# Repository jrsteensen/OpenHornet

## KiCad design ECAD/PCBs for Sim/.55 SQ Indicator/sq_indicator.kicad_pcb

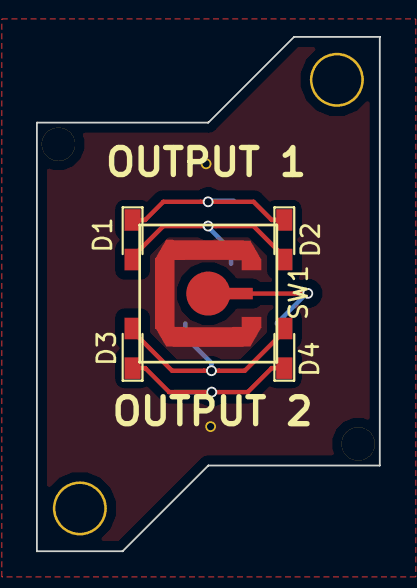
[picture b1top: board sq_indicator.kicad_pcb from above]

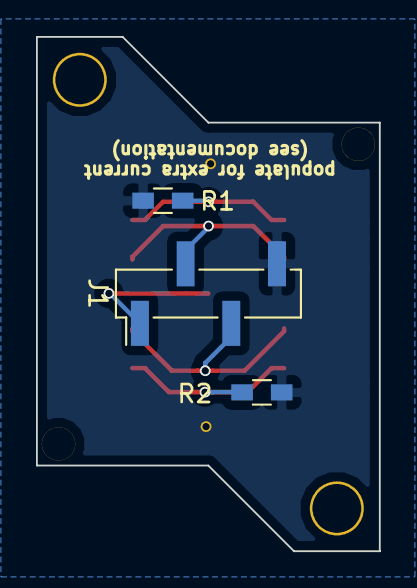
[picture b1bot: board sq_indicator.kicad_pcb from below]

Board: 2 copper layers, 19.1 x 28.6 mm, 8 parts (3 on the bottom side), 6 nets.

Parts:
D1, D2, D3, D4: LED; LED_0603_HandSoldering
J1: Conn_01x04; Pin_Header_Straight_1x04_Pitch2.54mm_SMD_Pin1Left
R1, R2: 68; R_0603_HandSoldering
SW1: push; SWITCH_SNAP_DOME_6.3mm_DIA_SINGLE_SIDE_PCB

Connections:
/backlight_1: D1.2, D2.2, J1.2
/backlight_2: D3.2, D4.2, J1.3
/button: J1.1, SW1.1
GND: J1.4, R1.1, R2.1, SW1.2
unnamed: D1.1, D2.1, R1.2
unnamed: D3.1, D4.1, R2.2

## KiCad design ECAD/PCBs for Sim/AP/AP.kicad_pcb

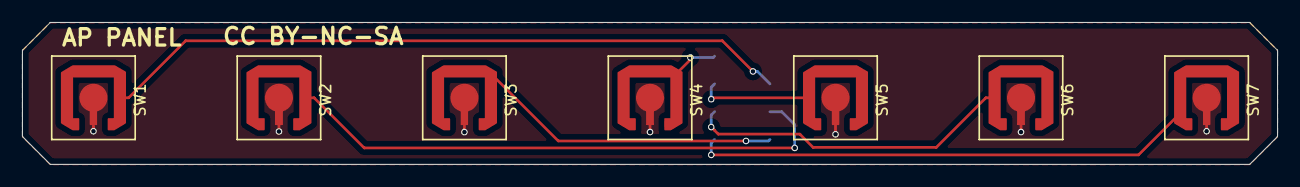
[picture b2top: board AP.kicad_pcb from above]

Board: 2 copper layers, 114.6 x 13.0 mm, 8 parts (1 on the bottom side), 8 nets.

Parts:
J1: Conn_02x04_Odd_Even; Pin_Header_Straight_2x04_Pitch2.54mm_SMD
SW1, SW2, SW3, SW4, SW5, SW6, SW7: SW_SPST; SWITCH_SNAP_DOME_6.3mm_DIA_SINGLE_SIDE_PCB

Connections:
unnamed: J1.1, SW1.1, SW2.1, SW3.1, SW4.1, SW5.1, SW6.1, SW7.1
unnamed: J1.2, SW4.2
unnamed: J1.3, SW1.2
unnamed: J1.4, SW5.2
unnamed: J1.5, SW2.2
unnamed: J1.6, SW6.2
unnamed: J1.7, SW3.2
unnamed: J1.8, SW7.2

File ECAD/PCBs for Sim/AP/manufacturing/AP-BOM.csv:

"Id";"Designator";"Package";"Quantity";"Designation";"Supplier and ref";
1;"SW1,SW2,SW3,SW4,SW5,SW6,SW7";"SWITCH_SNAP_DOME_6.3mm_DIA_SINGLE_SIDE_PCB";7;"SW_SPST";;;
2;"G***";"CC-BY-NC-SA-Small";1;"LOGO";;;
3;"G***";"OH_LOGO_37.7mm_5.9mm";1;"LOGO";;;
4;"J1";"Pin_Header_Straight_2x04_Pitch2.54mm_SMD";1;"Conn_02x04_Odd_Even";;;

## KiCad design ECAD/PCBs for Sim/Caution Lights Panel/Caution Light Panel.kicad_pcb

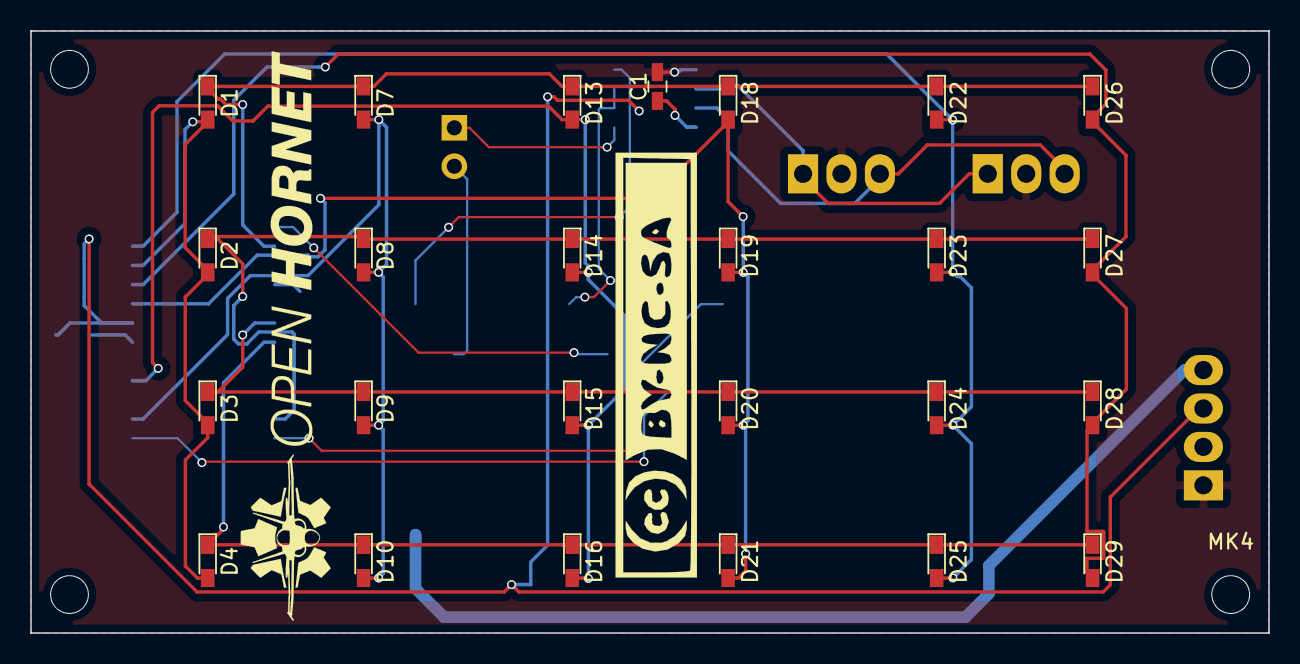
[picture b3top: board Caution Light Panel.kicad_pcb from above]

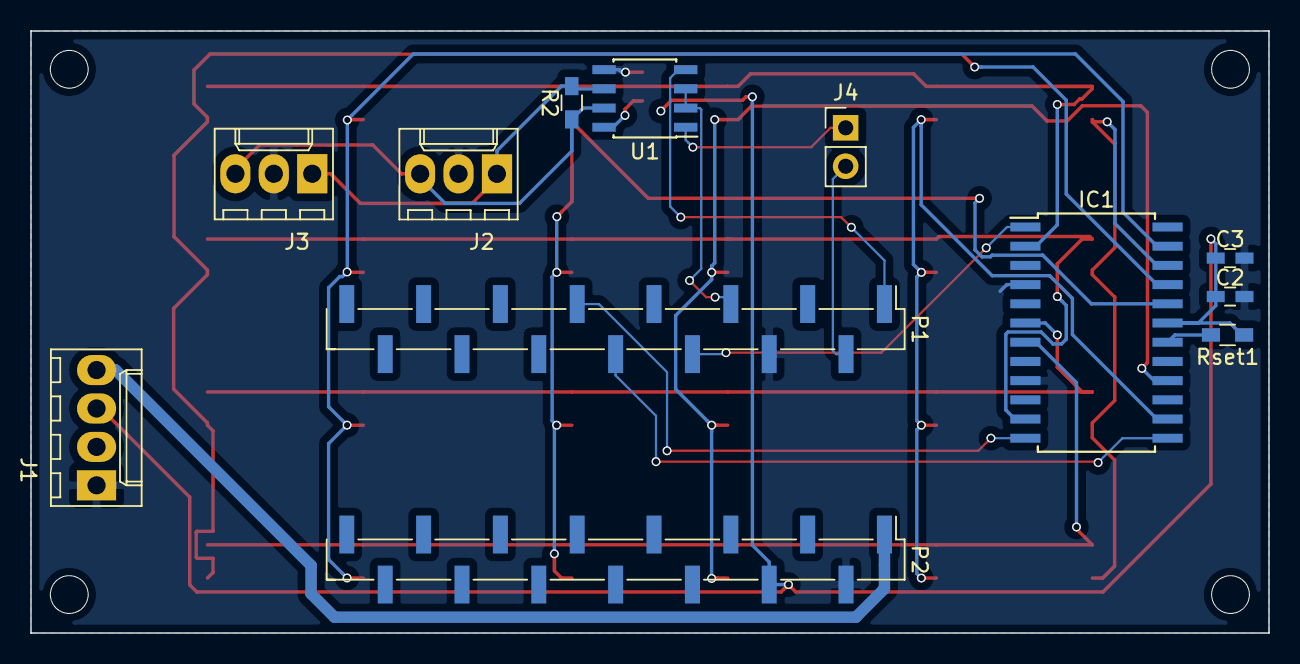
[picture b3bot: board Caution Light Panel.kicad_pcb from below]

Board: 2 copper layers, 81.9 x 39.8 mm, 41 parts (12 on the bottom side), 23 nets.

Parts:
C1: 0.1uF; C_0603_HandSoldering
C2: 100nF; C_0603_HandSoldering
C3: 47uF; C_0603_HandSoldering
D1: 0,0; LED_0603_HandSoldering
D2: 1,0; LED_0603_HandSoldering
D3: 2,0; LED_0603_HandSoldering
D4: 3,0; LED_0603_HandSoldering
D7: 0,1; LED_0603_HandSoldering
D8: 1,1; LED_0603_HandSoldering
D9: 2,1; LED_0603_HandSoldering
D10: 3,1; LED_0603_HandSoldering
D13: 0,2; LED_0603_HandSoldering
D14: 1,2; LED_0603_HandSoldering
D15: 2,2; LED_0603_HandSoldering
D16: 3,2; LED_0603_HandSoldering
D18: 0,3; LED_0603_HandSoldering
D19: 1.3; LED_0603_HandSoldering
D20: 2,3; LED_0603_HandSoldering
D21: 3,3; LED_0603_HandSoldering
D22: 0.4; LED_0603_HandSoldering
D23: 1.4; LED_0603_HandSoldering
D24: 2,4; LED_0603_HandSoldering
D25: 3,4; LED_0603_HandSoldering
D26: 0.5; LED_0603_HandSoldering
D27: 1.5; LED_0603_HandSoldering
D28: 2,5; LED_0603_HandSoldering
D29: 3,5; LED_0603_HandSoldering
IC1: MAX7219; SOIC-24W_7.5x15.4mm_Pitch1.27mm
J1: PWR; Molex_KK-6410-04_04x2.54mm_Straight
J2: BUS IN; Molex_KK-6410-03_03x2.54mm_Straight
J3: BUS OUT; Molex_KK-6410-03_03x2.54mm_Straight
J4: PGM ENBLE; Pin_Header_Straight_1x02_Pitch2.54mm
MK1, MK2, MK3, MK4: Mounting_Hole; MountingHole_2.5mm
P1: Digital; Pin_Header_Straight_1x15_Pitch2.54mm_SMD_Pin1Left
P2: Analog; Pin_Header_Straight_1x15_Pitch2.54mm_SMD_Pin1Left
R2: 120; R_0603_HandSoldering
Rset1: 30K; R_0603_HandSoldering
U1: MAX487EESA; SOIC-8_3.9x4.9mm_Pitch1.27mm

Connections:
+5V: C1.1, C2.1, C3.1, IC1.19, J1.3, P2.4, Rset1.1, U1.8
+12V: J1.4, P2.1
/0(Rx): J4.2, P1.2
/1(Tx): P1.1, U1.4
/2: P1.5, U1.2, U1.3
/3(**): IC1.1, P1.6
/5(**): IC1.13, P1.8
/6(**): IC1.12, P1.9
/Dig0: D1.1, D7.1, D13.1, D18.1, D22.1, D26.1, IC1.2
/Dig1: D2.1, D8.1, D14.1, D19.1, D23.1, D27.1, IC1.11
/Dig2: D3.1, D9.1, D15.1, D20.1, D24.1, D28.1, IC1.6
/Dig3: D4.1, D10.1, D16.1, D21.1, D25.1, D29.1, IC1.7
/RX_ENABLE: J4.1, U1.1
/SegA: D7.2, D8.2, D9.2, D10.2, IC1.14
/SegB: D13.2, D14.2, D15.2, D16.2, IC1.16
/SegC: D18.2, D19.2, D20.2, D21.2, IC1.20
/SegD: D22.2, D23.2, D24.2, D25.2, IC1.23
/SegDP: D1.2, D2.2, D3.2, D4.2, IC1.22
/SegE: D26.2, D27.2, D28.2, D29.2, IC1.21
GND: C1.2, C2.2, C3.2, IC1.4, IC1.9, J1.1, J2.2, J3.2, P1.4, P2.2, U1.5
unnamed: IC1.18, Rset1.2
unnamed: J2.1, J3.1, R2.2, U1.6
unnamed: J2.3, J3.3, R2.1, U1.7

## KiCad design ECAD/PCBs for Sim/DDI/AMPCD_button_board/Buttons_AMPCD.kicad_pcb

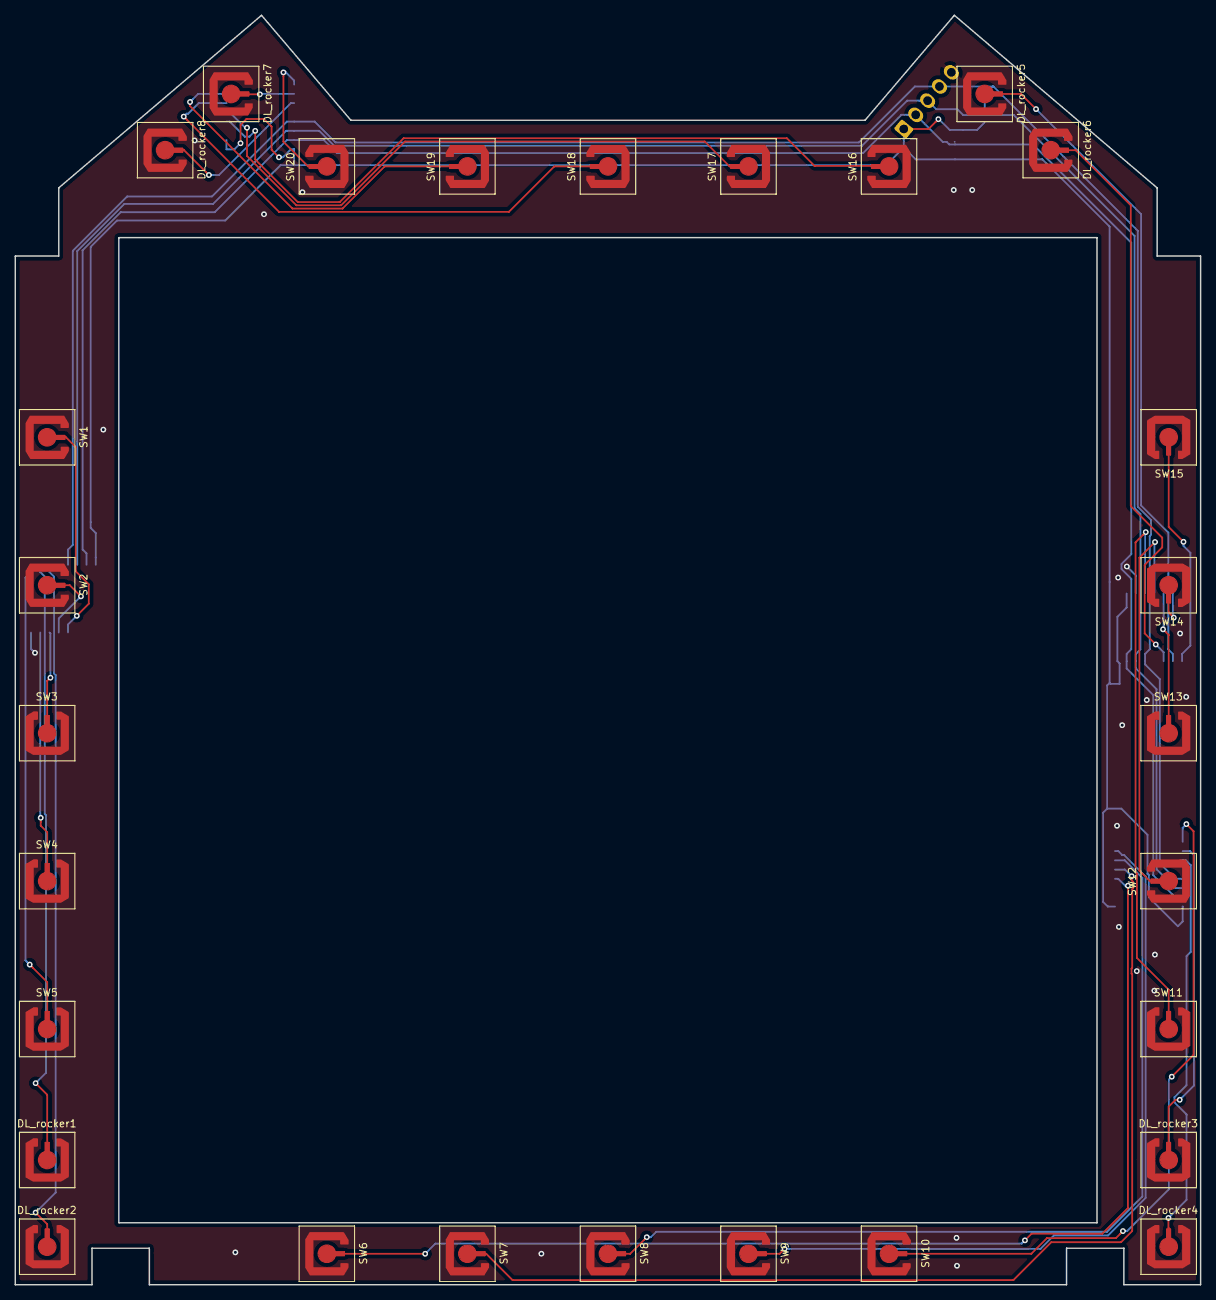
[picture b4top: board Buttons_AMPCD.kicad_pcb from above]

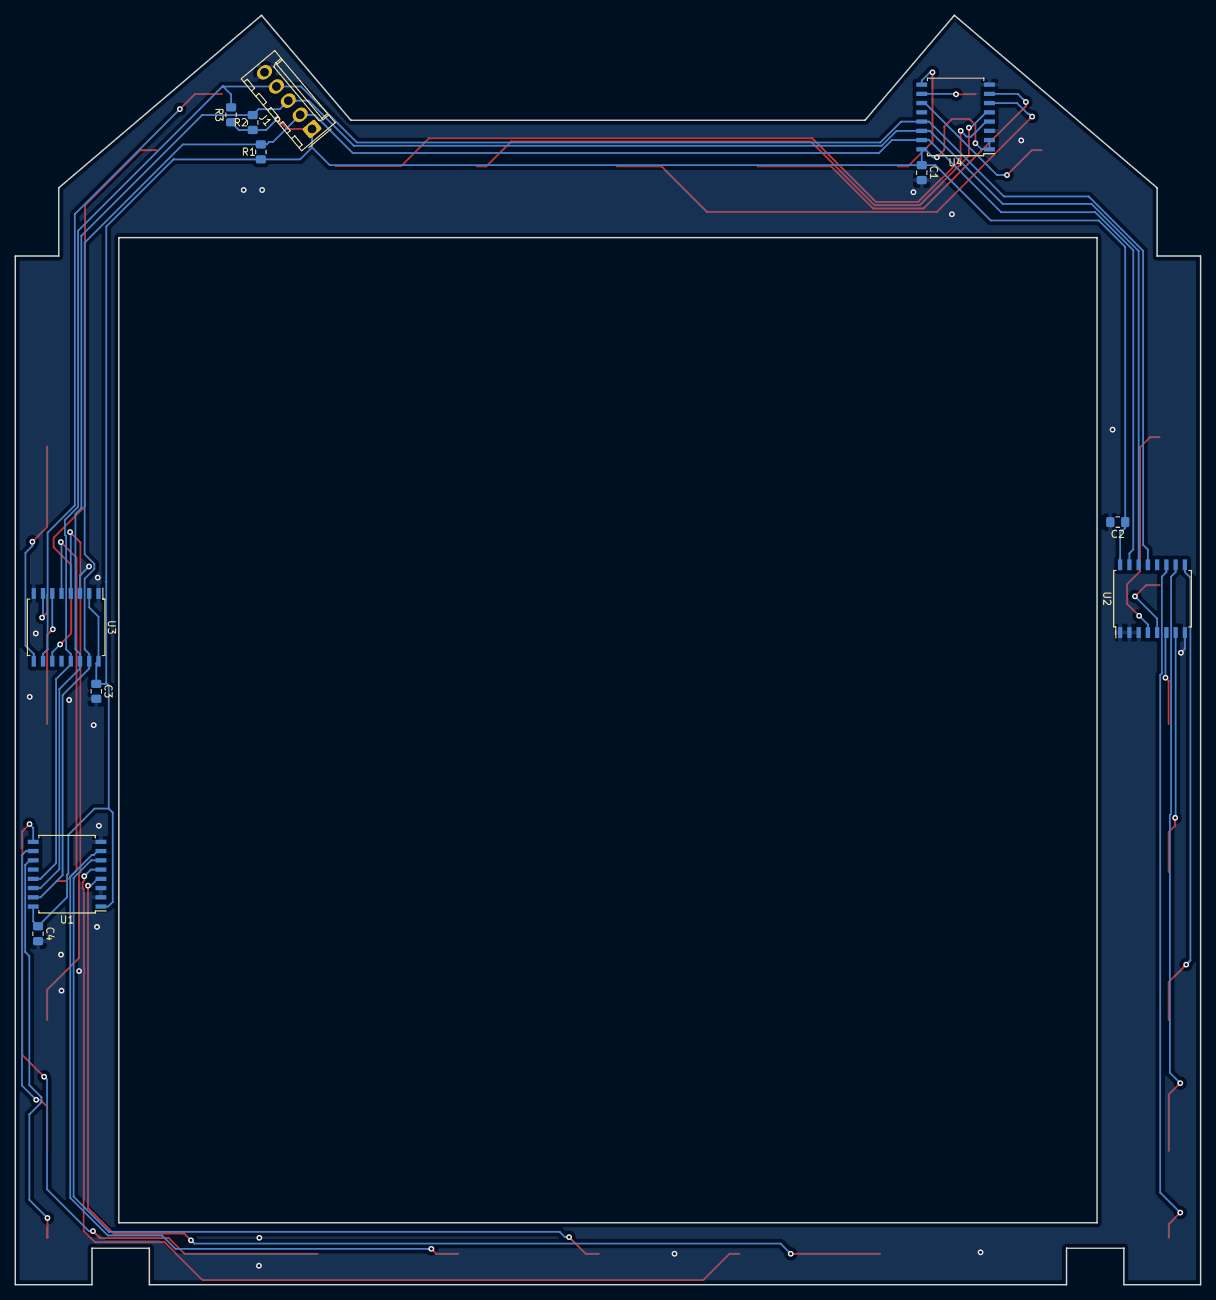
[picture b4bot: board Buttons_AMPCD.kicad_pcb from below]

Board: 2 copper layers, 162.8 x 174.4 mm, 40 parts (12 on the bottom side), 33 nets.

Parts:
C1, C2, C3, C4: 47uF; C_0805_2012Metric_Pad1.15x1.40mm_HandSolder
DL_rocker1, DL_rocker2, DL_rocker3, DL_rocker4, DL_rocker5, DL_rocker6, DL_rocker7, DL_rocker8: SW_Push; SWITCH_SNAP_DOME_6.3mm_DIA_SINGLE_SIDE_PCB
J1: ExpansionPort; Molex_KK-254_AE-6410-05A_1x05_P2.54mm_Vertical
R1, R2, R3: 1k; R_0805_2012Metric_Pad1.15x1.40mm_HandSolder
SW1, SW2, SW3, SW4, SW5, SW6, SW7, SW8, SW9, SW10, SW11, SW12, SW13, SW14, SW15, SW16, SW17, SW18, SW19, SW20: SW_Push; SWITCH_SNAP_DOME_6.3mm_DIA_SINGLE_SIDE_PCB
U1, U2, U3, U4: TCA9534; SOIC-16W_7.5x10.3mm_P1.27mm

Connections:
+5V: C1.1, C2.1, C3.1, C4.1, J1.1, R1.1, R2.1, R3.1, U1.1, U1.16, U2.16, U3.2, U3.16, U4.1, U4.2, U4.16
GND: C1.2, C2.2, C3.2, C4.2, DL_rocker1.2, DL_rocker2.2, DL_rocker3.2, DL_rocker4.2, DL_rocker5.2, DL_rocker6.2, DL_rocker7.2, DL_rocker8.2, J1.5, SW1.2, SW2.2, SW3.2, SW4.2, SW5.2, SW6.2, SW7.2, SW8.2, SW9.2, SW10.2, SW11.2, SW12.2, SW13.2, SW14.2, SW15.2, SW16.2, SW17.2, SW18.2, SW19.2, SW20.2, U1.2, U1.3, U1.8, U2.1, U2.2, U2.3, U2.8, U3.1, U3.3, U3.8, U4.3, U4.8
IRQ: J1.4, R3.2, U1.13, U2.13, U3.13, U4.13
unnamed: DL_rocker1.1, U2.10
unnamed: DL_rocker2.1, U2.11
unnamed: DL_rocker3.1, U1.10
unnamed: DL_rocker4.1, U1.11
unnamed: DL_rocker5.1, U3.10
unnamed: DL_rocker6.1, U3.11
unnamed: DL_rocker7.1, U4.10
unnamed: DL_rocker8.1, U4.11
unnamed: SW1.1, U2.4
unnamed: SW2.1, U2.5
unnamed: SW3.1, U2.6
unnamed: SW4.1, U2.7
unnamed: SW5.1, U2.9
unnamed: SW6.1, U1.4
unnamed: SW7.1, U1.5
unnamed: SW8.1, U1.6
unnamed: SW9.1, U1.7
unnamed: SW10.1, U1.9
unnamed: SW11.1, U3.4
unnamed: SW12.1, U3.5
unnamed: SW13.1, U3.6
unnamed: SW14.1, U3.7
unnamed: SW15.1, U3.9
unnamed: SW16.1, U4.4
unnamed: SW17.1, U4.5
unnamed: SW18.1, U4.6
unnamed: SW19.1, U4.7
unnamed: SW20.1, U4.9
SCL: J1.3, R2.2, U1.14, U2.14, U3.14, U4.14
SDA: J1.2, R1.2, U1.15, U2.15, U3.15, U4.15

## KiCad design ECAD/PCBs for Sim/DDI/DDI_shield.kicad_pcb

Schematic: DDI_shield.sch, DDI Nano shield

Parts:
C1: 0.1uF; C_0805_2012Metric_Pad1.15x1.40mm_HandSolder
J1: PWR; Molex_KK-254_AE-6410-04A_1x04_P2.54mm_Vertical
J2: BUS IN; Molex_KK-254_AE-6410-03A_1x03_P2.54mm_Vertical
J3: BUS OUT; Molex_KK-254_AE-6410-03A_1x03_P2.54mm_Vertical
J4: PGM SEL; Pin_Header_Straight_1x02_Pitch2.54mm
J5: POT1; Molex_KK-254_AE-6410-03A_1x03_P2.54mm_Vertical
J6: ExpansionPort; PinHeader_1x05_P2.54mm_Vertical
J7: POT2; Molex_KK-254_AE-6410-03A_1x03_P2.54mm_Vertical
J8: ROT SW; PinHeader_1x04_P2.54mm_Vertical
J9: CRS; PinHeader_1x03_P2.54mm_Vertical
J10: HDG; PinHeader_1x03_P2.54mm_Vertical
P1: Digital; Socket_Strip_Arduino_1x15
P2: Analog; Socket_Strip_Arduino_1x15
P3, P4, P5, P6: mounting; 1pin_Nano
R1: 120; R_0805_2012Metric_Pad1.15x1.40mm_HandSolder
R2, R3, R4, R5: 10k; R_0805_2012Metric_Pad1.15x1.40mm_HandSolder
U1: MAX487EESA; SOIC-8_3.9x4.9mm_Pitch1.27mm

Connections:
+3V3: J1.2, P2.14
+5V: C1.1, J1.3, J5.1, J6.1 (Power), J7.1, P2.4, R2.1, R4.1, U1.8
+12V: J1.4, P2.1
/0(Rx): J4.2, P1.2
/1(Tx): P1.1, U1.4
/2: P1.5, U1.2, U1.3
/3(**): J6.4 (IRQ), P1.6
/4: J6.2 (SDA), P1.7
/5(**): J6.3 (SCL), P1.8
/8: P1.11, R2.2, R3.1
/9(**): P1.12, R4.2, R5.1
/10(**/SS): J8.1, P1.13
/11(**/MOSI): J8.2, P1.14
/12(MISO): J8.3, P1.15
/A0: J5.2, P2.12
/A1: J7.2, P2.11
/A3: J9.1, P2.9
/A4: J9.3, P2.8
/A5: J10.1, P2.7
/A6: J10.3, P2.6
/AREF: P2.13
/RX_ENABLE: J4.1, U1.1
GND: C1.2, J1.1, J2.2, J3.2, J5.3, J6.5 (GND), J7.3, J8.4, J9.2, J10.2, P1.4, P2.2, R3.2, R5.2, U1.5
unnamed: J2.1, J3.1, R1.2, U1.6
unnamed: J2.3, J3.3, R1.1, U1.7

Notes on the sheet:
Holes
NANO CONNECTIONS
RS-485 BUS
1) INSTALL 120 OHM RESISTOR ACROSS A AND B OF MAX487 ONLY FOR BUS TERMINATION. 2) INSTALL JUMPER BETWEEN PIN 1 AND 2 OF PGM SEL FOR RS487 BUS ENABLE. REMOVE JUMPER FOR PROGRAMMING ARDUINO NANO. 3) SEE DOCUMENTATION FOR CONNECTIVITY AND CONFIGURATION.
NOTES: (UNLESS OTHERWISE SPECIFIED)
PWR IN
PWR FLAGS
Inputs
I2C addresses 0b0111000 0b0111001 0b0111010 0b0111011
DEVICE differentiation see documentation
13(SCK)
6(**)

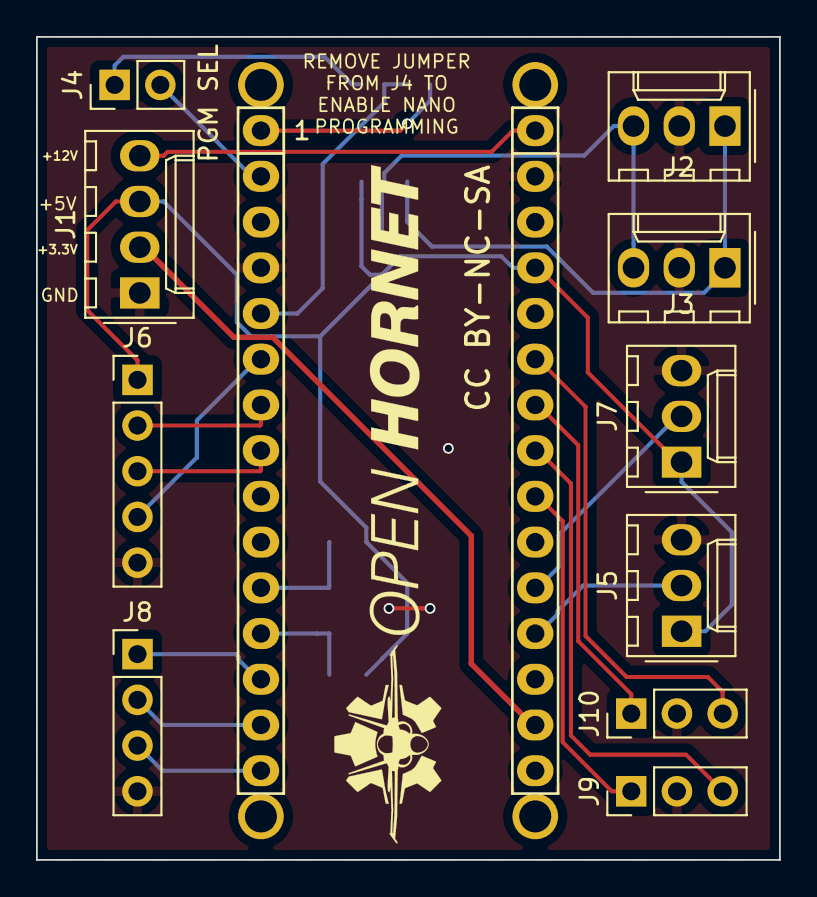
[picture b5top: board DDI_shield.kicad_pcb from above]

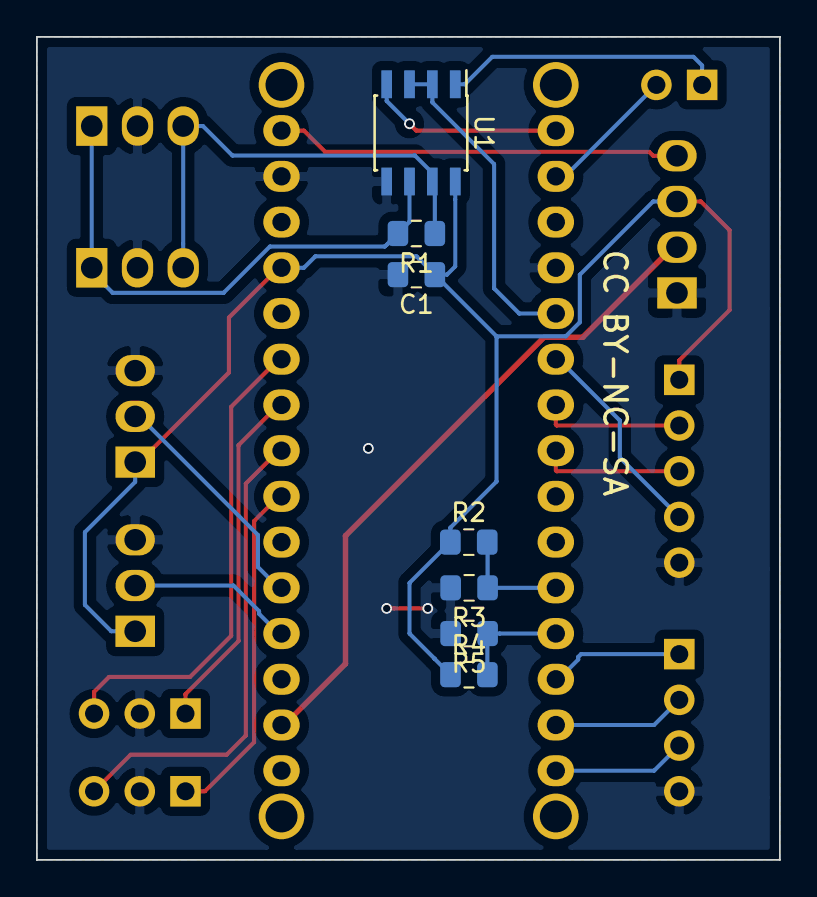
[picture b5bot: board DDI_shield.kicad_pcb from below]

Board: 2 copper layers, 41.3 x 45.7 mm, 23 parts (7 on the bottom side), 24 nets.

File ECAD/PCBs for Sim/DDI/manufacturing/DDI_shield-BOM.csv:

"Id";"Designator";"Package";"Quantity";"Designation";"Supplier and ref";
1;"G***";"OH_LOGO_37.7mm_5.9mm";1;"LOGO";;;
2;"J8";"PinHeader_1x04_P2.54mm_Vertical";1;"ROT SW";;;
3;"J4";"Pin_Header_Straight_1x02_Pitch2.54mm";1;"PGM SEL";;;
4;"P1";"Socket_Strip_Arduino_1x15";1;"Digital";;;
5;"P2";"Socket_Strip_Arduino_1x15";1;"Analog";;;
6;"P3,P4,P5,P6";"1pin_Nano";4;"mounting";;;
7;"U1";"SOIC-8_3.9x4.9mm_Pitch1.27mm";1;"MAX487EESA";;;
8;"J6";"PinHeader_1x05_P2.54mm_Vertical";1;"ExpansionPort";;;
9;"R2,R3,R4,R5";"R_0805_2012Metric_Pad1.15x1.40mm_HandSolder";4;"10k";;;
10;"C1";"C_0805_2012Metric_Pad1.15x1.40mm_HandSolder";1;"0.1uF";;;
11;"J1";"Molex_KK-254_AE-6410-04A_1x04_P2.54mm_Vertical";1;"PWR";;;
12;"J2";"Molex_KK-254_AE-6410-03A_1x03_P2.54mm_Vertical";1;"BUS IN";;;
13;"J3";"Molex_KK-254_AE-6410-03A_1x03_P2.54mm_Vertical";1;"BUS OUT";;;
14;"J5";"Molex_KK-254_AE-6410-03A_1x03_P2.54mm_Vertical";1;"POT1";;;
15;"J7";"Molex_KK-254_AE-6410-03A_1x03_P2.54mm_Vertical";1;"POT2";;;
16;"R1";"R_0805_2012Metric_Pad1.15x1.40mm_HandSolder";1;"120";;;
17;"J9";"PinHeader_1x03_P2.54mm_Vertical";1;"CRS";;;
18;"J10";"PinHeader_1x03_P2.54mm_Vertical";1;"HDG";;;

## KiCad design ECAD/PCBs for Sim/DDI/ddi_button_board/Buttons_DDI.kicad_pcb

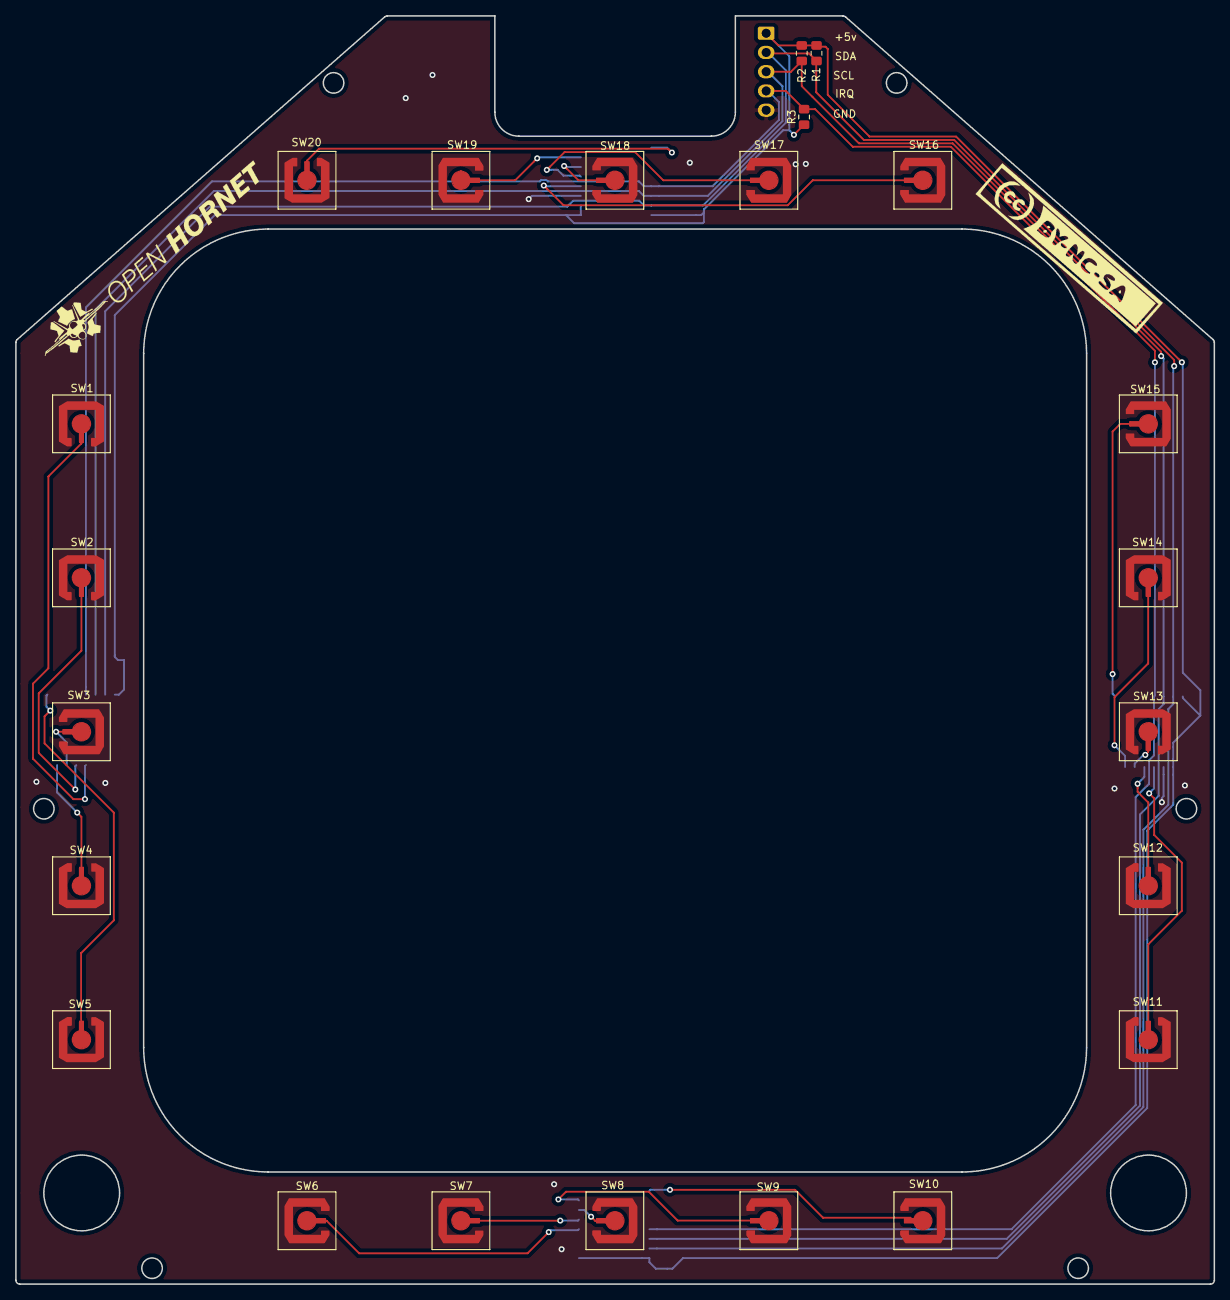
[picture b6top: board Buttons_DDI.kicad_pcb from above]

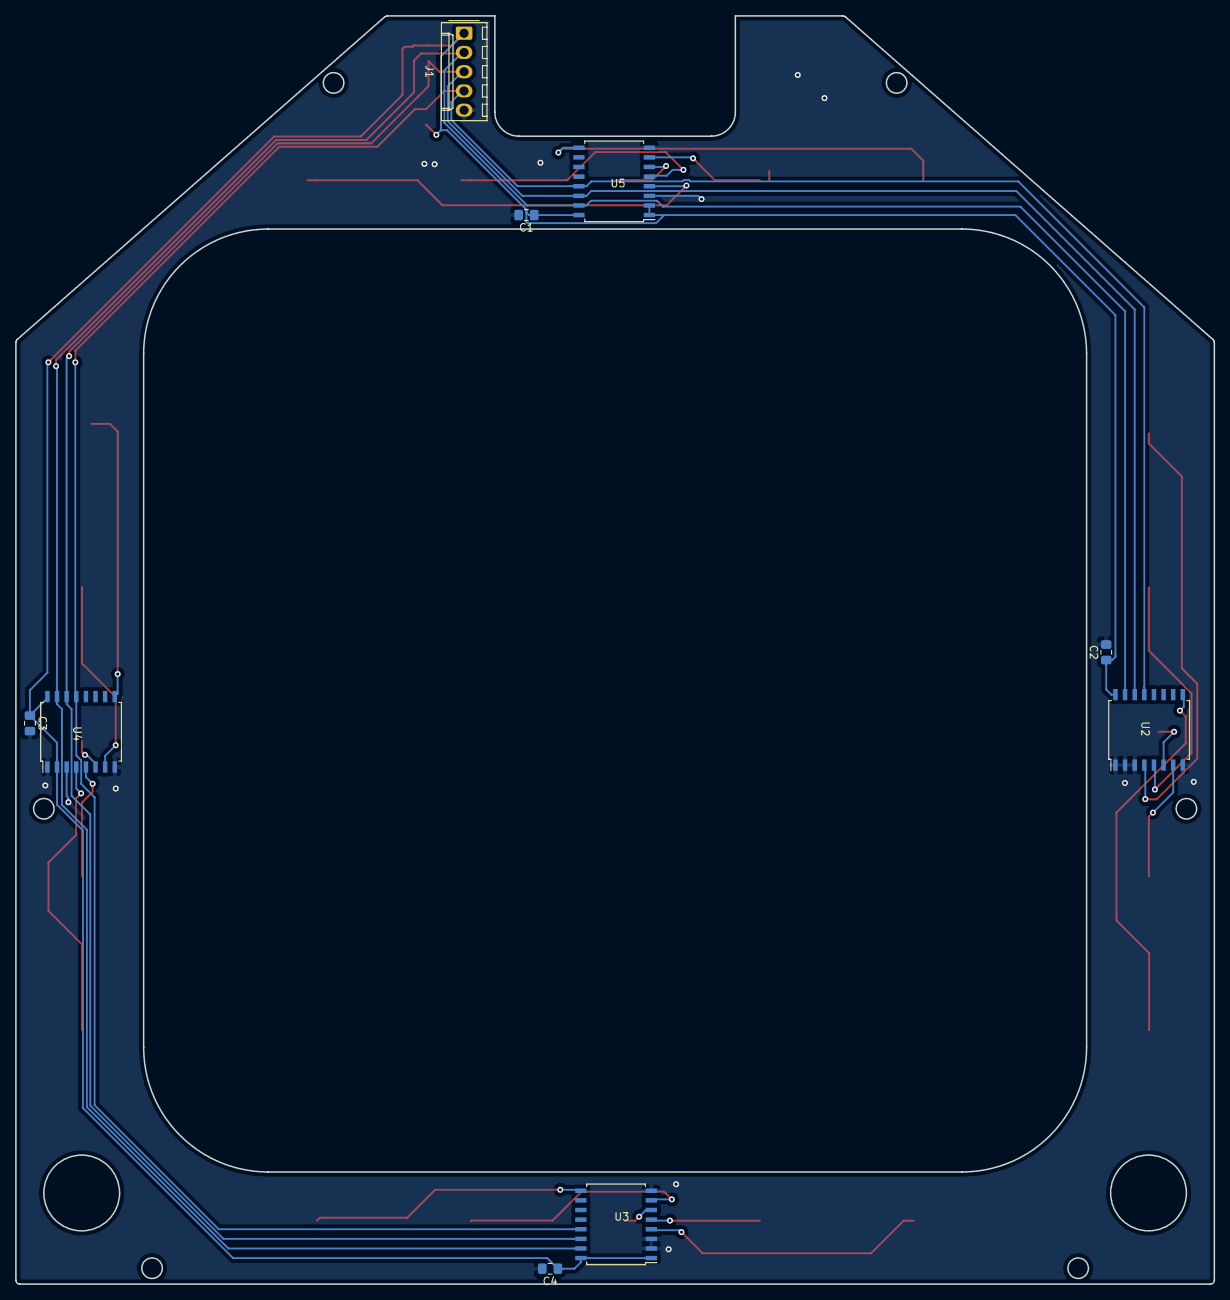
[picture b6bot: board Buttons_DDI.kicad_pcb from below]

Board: 2 copper layers, 158.2 x 167.4 mm, 32 parts (9 on the bottom side), 25 nets.

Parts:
C1, C2, C3, C4: 47uF; C_0805_2012Metric_Pad1.15x1.40mm_HandSolder
J1: ExpansionPort; Molex_KK-254_AE-6410-05A_1x05_P2.54mm_Vertical
R1, R2, R3: 1k; R_0805_2012Metric_Pad1.15x1.40mm_HandSolder
SW1, SW2, SW3, SW4, SW5, SW6, SW7, SW8, SW9, SW10, SW11, SW12, SW13, SW14, SW15, SW16, SW17, SW18, SW19, SW20: SW_Push; SWITCH_SNAP_DOME_6.3mm_DIA_SINGLE_SIDE_PCB
U2, U3, U4, U5: TCA9534; SOIC-16W_7.5x10.3mm_P1.27mm

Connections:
+5V: C1.1, C2.1, C3.1, C4.1, J1.1, R1.1, R2.1, R3.1, U2.16, U3.1, U3.16, U4.2, U4.16, U5.1, U5.2, U5.16
GND: C1.2, C2.2, C3.2, C4.2, J1.5, SW1.2, SW2.2, SW3.2, SW4.2, SW5.2, SW6.2, SW7.2, SW8.2, SW9.2, SW10.2, SW11.2, SW12.2, SW13.2, SW14.2, SW15.2, SW16.2, SW17.2, SW18.2, SW19.2, SW20.2, U2.1, U2.2, U2.3, U2.8, U3.2, U3.3, U3.8, U4.1, U4.3, U4.8, U5.3, U5.8
IRQ: J1.4, R3.2, U2.13, U3.13, U4.13, U5.13
unnamed: SW1.1, U2.4
unnamed: SW2.1, U2.5
unnamed: SW3.1, U2.6
unnamed: SW4.1, U2.7
unnamed: SW5.1, U2.9
unnamed: SW6.1, U3.4
unnamed: SW7.1, U3.5
unnamed: SW8.1, U3.6
unnamed: SW9.1, U3.7
unnamed: SW10.1, U3.9
unnamed: SW11.1, U4.4
unnamed: SW12.1, U4.5
unnamed: SW13.1, U4.6
unnamed: SW14.1, U4.7
unnamed: SW15.1, U4.9
unnamed: SW16.1, U5.4
unnamed: SW17.1, U5.5
unnamed: SW18.1, U5.6
unnamed: SW19.1, U5.7
unnamed: SW20.1, U5.9
SCL: J1.3, R2.2, U2.14, U3.14, U4.14, U5.14
SDA: J1.2, R1.2, U2.15, U3.15, U4.15, U5.15

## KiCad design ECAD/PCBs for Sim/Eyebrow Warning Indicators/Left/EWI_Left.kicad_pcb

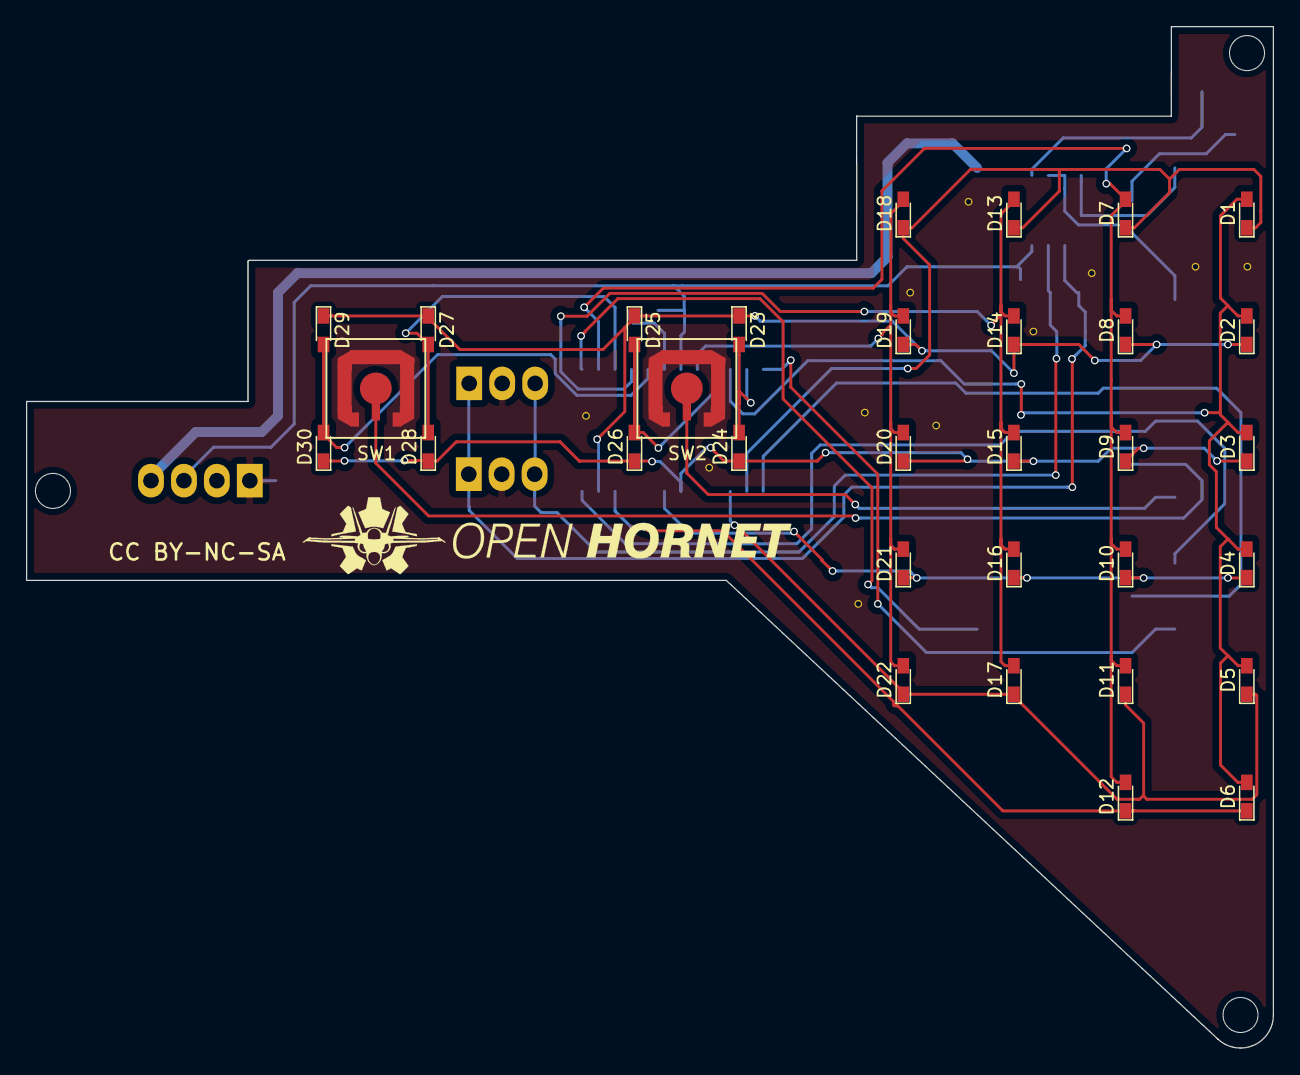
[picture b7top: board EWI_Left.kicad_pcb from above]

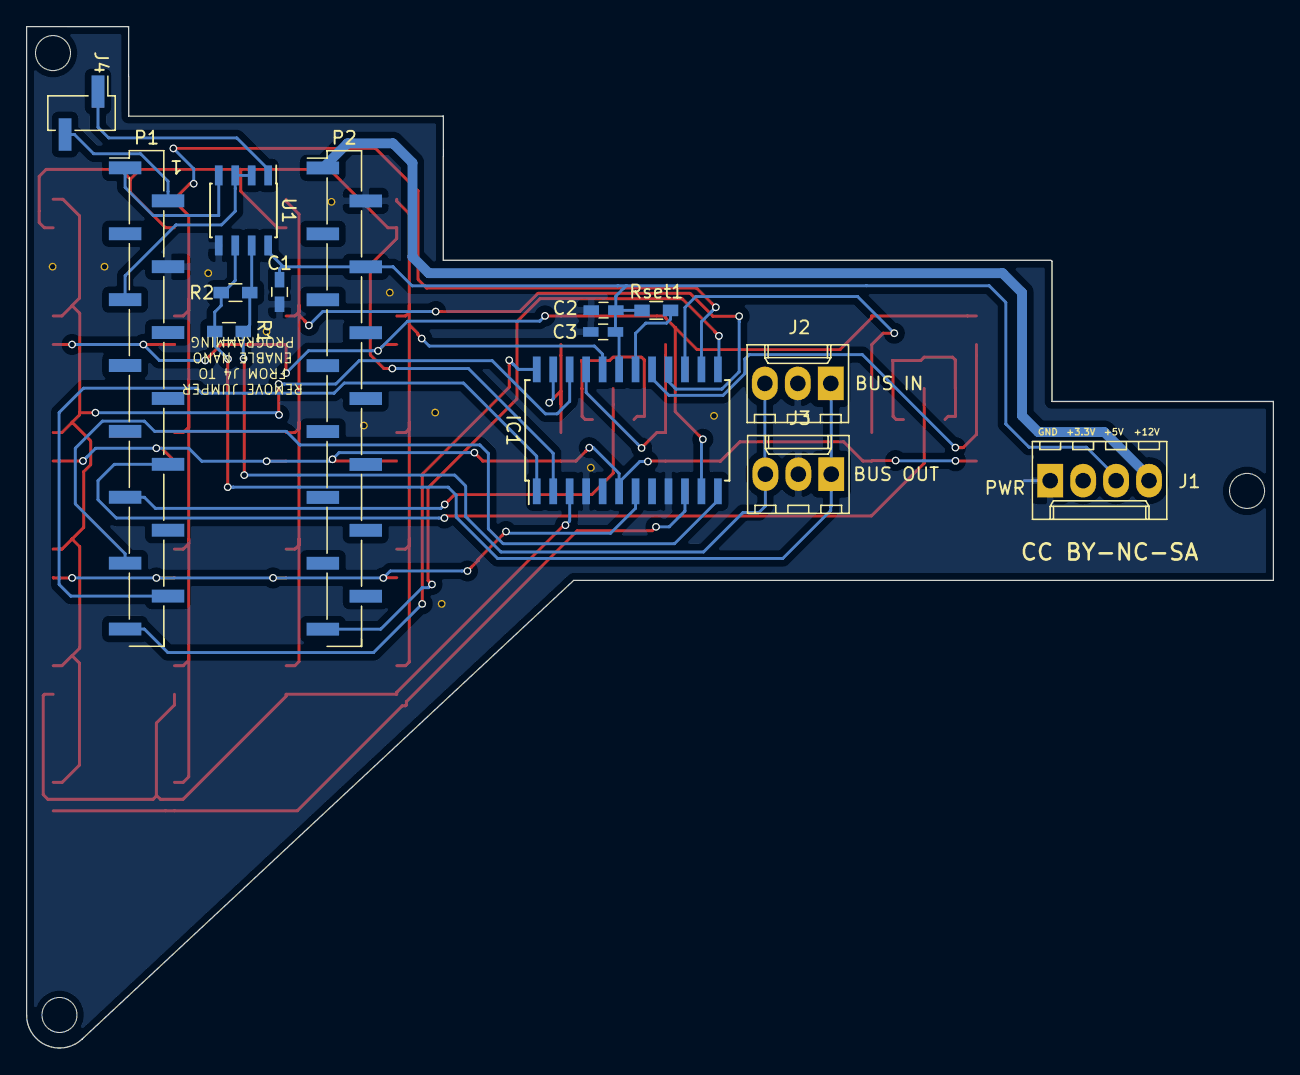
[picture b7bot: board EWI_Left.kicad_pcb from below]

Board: 2 copper layers, 96.1 x 78.8 mm, 49 parts (14 on the bottom side), 30 nets.

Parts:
C1: 0.1uF; C_0603_HandSoldering
C2: 100nF; C_0603_HandSoldering
C3: 47uF; C_0603_HandSoldering
D1: 0,0; LED_0603_HandSoldering
D2: 1,0; LED_0603_HandSoldering
D3: 2,0; LED_0603_HandSoldering
D4: 3,0; LED_0603_HandSoldering
D5: 4,0; LED_0603_HandSoldering
D6: 5,0; LED_0603_HandSoldering
D7: 0,1; LED_0603_HandSoldering
D8: 1,1; LED_0603_HandSoldering
D9: 2,1; LED_0603_HandSoldering
D10: 3,1; LED_0603_HandSoldering
D11: 4,1; LED_0603_HandSoldering
D12: 5,1; LED_0603_HandSoldering
D13: 0,2; LED_0603_HandSoldering
D14: 1,2; LED_0603_HandSoldering
D15: 2,2; LED_0603_HandSoldering
D16: 3,2; LED_0603_HandSoldering
D17: 4,2; LED_0603_HandSoldering
D18: 0,3; LED_0603_HandSoldering
D19: 1.3; LED_0603_HandSoldering
D20: 2,3; LED_0603_HandSoldering
D21: 3,3; LED_0603_HandSoldering
D22: 4,3; LED_0603_HandSoldering
D23: 1.4; LED_0603_HandSoldering
D24: 2,4; LED_0603_HandSoldering
D25: 1.5; LED_0603_HandSoldering
D26: 2,5; LED_0603_HandSoldering
D27: 1.6; LED_0603_HandSoldering
D28: 2,6; LED_0603_HandSoldering
D29: 1.7; LED_0603_HandSoldering
D30: 2,7; LED_0603_HandSoldering
IC1: MAX7219; SOIC-24W_7.5x15.4mm_Pitch1.27mm
J1: PWR; Molex_KK-6410-04_04x2.54mm_Straight
J2: BUS IN; Molex_KK-6410-03_03x2.54mm_Straight
J3: BUS OUT; Molex_KK-6410-03_03x2.54mm_Straight
J4: PGM ENBLE; Pin_Header_Straight_1x02_Pitch2.54mm_SMD_Pin1Left
MK1, MK2, MK3: Mounting_Hole; MountingHole_2.7mm_M2.5_ISO14580
P1: Digital; Pin_Header_Straight_1x15_Pitch2.54mm_SMD_Pin1Left
P2: Analog; Pin_Header_Straight_1x15_Pitch2.54mm_SMD_Pin1Left
R1, R2: 120; R_0603_HandSoldering
Rset1: 30K; R_0603_HandSoldering
SW1: IN SWTCH; SWITCH_SNAP_DOME_6.3mm_DIA_SINGLE_SIDE_PCB
SW2: OUT SWTCH; SWITCH_SNAP_DOME_6.3mm_DIA_SINGLE_SIDE_PCB
U1: MAX487EESA; SOIC-8_3.9x4.9mm_Pitch1.27mm

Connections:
+5V: C1.1, C2.1, C3.1, IC1.19, J1.3, P2.4, Rset1.1, U1.8
+12V: J1.4, P2.1
/0(Rx): J4.2, P1.2
/1(Tx): P1.1, U1.4
/2: P1.5, U1.2, U1.3
/7: P1.10, SW1.1
/8: P1.11, SW2.1
/10(**/SS): IC1.12, P1.13
/11(**/MOSI): IC1.1, P1.14
/12(MISO): IC1.24, P1.15
/13(SCK): IC1.13, P2.15
/Dig0: D1.1, D7.1, D13.1, D18.1, IC1.2
/Dig1: D2.1, D8.1, D14.1, D19.1, D23.1, D25.1, D27.1, D29.1, IC1.11
/Dig2: D3.1, D9.1, D15.1, D20.1, D24.1, D26.1, D28.1, D30.1, IC1.6
/Dig3: D4.1, D10.1, D16.1, D21.1, IC1.7
/Dig4: D5.1, D11.1, D17.1, D22.1, IC1.3
/Dig5: D6.1, D12.1, IC1.10
/RX_ENABLE: J4.1, U1.1
/SegA: D7.2, D8.2, D9.2, D10.2, D11.2, D12.2, IC1.14
/SegB: D13.2, D14.2, D15.2, D16.2, D17.2, IC1.16
/SegC: D18.2, D19.2, D20.2, D21.2, D22.2, IC1.20
/SegD: D23.2, D24.2, IC1.23
/SegDP: D1.2, D2.2, D3.2, D4.2, D5.2, D6.2, IC1.22
/SegE: D25.2, D26.2, IC1.21
/SegF: D27.2, D28.2, IC1.15
/SegG: D29.2, D30.2, IC1.17
GND: C1.2, C2.2, C3.2, IC1.4, IC1.9, J1.1, J2.2, J3.2, P1.4, P2.2, SW1.2, SW2.2, U1.5
unnamed: IC1.18, Rset1.2
unnamed: J2.1, J3.1, R1.2, R2.2, U1.6
unnamed: J2.3, J3.3, R1.1, R2.1, U1.7

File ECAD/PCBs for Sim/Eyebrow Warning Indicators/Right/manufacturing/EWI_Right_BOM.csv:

"Id";"Designator";"Package";"Quantity";"Designation";"Supplier and ref";
1;"G***";"OH_LOGO_37.7mm_5.9mm";1;"LOGO";;;
2;"REF**,REF**,REF**,REF**,REF**,REF**,REF**,REF**,REF**,REF**,REF**,REF**,REF**";"via0.6";13;"via0.6";;;
3;"J1";"Molex_KK-6410-04_04x2.54mm_Straight";1;"PWR";;;
4;"C1";"C_0603_HandSoldering";1;"0.1uF";;;
5;"R1,R2";"R_0603_HandSoldering";2;"120";;;
6;"U1";"SOIC-8_3.9x4.9mm_Pitch1.27mm";1;"MAX487EESA";;;
7;"J2";"Molex_KK-6410-03_03x2.54mm_Straight";1;"BUS IN";;;
8;"J3";"Molex_KK-6410-03_03x2.54mm_Straight";1;"BUS OUT";;;
9;"MK1,MK2,MK3";"MountingHole_2.7mm_M2.5_ISO14580";3;"Mounting_Hole";;;
10;"C2";"C_0603_HandSoldering";1;"100nF";;;
11;"C3";"C_0603_HandSoldering";1;"47uF";;;
12;"D1";"LED_0603_HandSoldering";1;"0,0";;;
13;"D2";"LED_0603_HandSoldering";1;"1,0";;;
14;"D3";"LED_0603_HandSoldering";1;"2,0";;;
15;"D4";"LED_0603_HandSoldering";1;"3,0";;;
16;"D5";"LED_0603_HandSoldering";1;"4,0";;;
17;"D6";"LED_0603_HandSoldering";1;"5,0";;;
18;"D7";"LED_0603_HandSoldering";1;"0,1";;;
19;"D8";"LED_0603_HandSoldering";1;"1,1";;;
20;"D9";"LED_0603_HandSoldering";1;"2,1";;;
21;"D10";"LED_0603_HandSoldering";1;"3,1";;;
22;"D11";"LED_0603_HandSoldering";1;"4,1";;;
23;"D12";"LED_0603_HandSoldering";1;"5,1";;;
24;"D13";"LED_0603_HandSoldering";1;"0,2";;;
25;"D14";"LED_0603_HandSoldering";1;"1,2";;;
26;"D15";"LED_0603_HandSoldering";1;"2,2";;;
27;"D16";"LED_0603_HandSoldering";1;"3,2";;;
28;"D17";"LED_0603_HandSoldering";1;"4,2";;;
29;"D18";"LED_0603_HandSoldering";1;"0,3";;;
30;"D19";"LED_0603_HandSoldering";1;"1.3";;;
31;"D20";"LED_0603_HandSoldering";1;"2,3";;;
32;"D21";"LED_0603_HandSoldering";1;"3,3";;;
33;"D22";"LED_0603_HandSoldering";1;"4,3";;;
34;"D23";"LED_0603_HandSoldering";1;"1.4";;;
35;"D24";"LED_0603_HandSoldering";1;"2,4";;;
36;"D25";"LED_0603_HandSoldering";1;"1.5";;;
37;"D26";"LED_0603_HandSoldering";1;"2,5";;;
38;"D27";"LED_0603_HandSoldering";1;"1.6";;;
39;"D28";"LED_0603_HandSoldering";1;"2,6";;;
40;"D29";"LED_0603_HandSoldering";1;"1.7";;;
41;"D30";"LED_0603_HandSoldering";1;"2,7";;;
42;"IC1";"SOIC-24W_7.5x15.4mm_Pitch1.27mm";1;"MAX7219";;;
43;"Rset1";"R_0603_HandSoldering";1;"30K";;;
44;"SW1";"SWITCH_SNAP_DOME_6.3mm_DIA_SINGLE_SIDE_PCB";1;"IN SWTCH";;;
45;"SW2";"SWITCH_SNAP_DOME_6.3mm_DIA_SINGLE_SIDE_PCB";1;"OUT SWTCH";;;
46;"P2";"Pin_Header_Straight_1x15_Pitch2.54mm_SMD_Pin1Left";1;"Analog";;;
47;"P1";"Pin_Header_Straight_1x15_Pitch2.54mm_SMD_Pin1Left";1;"Digital";;;
48;"J4";"Pin_Header_Straight_1x02_Pitch2.54mm_SMD_Pin1Left";1;"PGM ENBLE";;;
